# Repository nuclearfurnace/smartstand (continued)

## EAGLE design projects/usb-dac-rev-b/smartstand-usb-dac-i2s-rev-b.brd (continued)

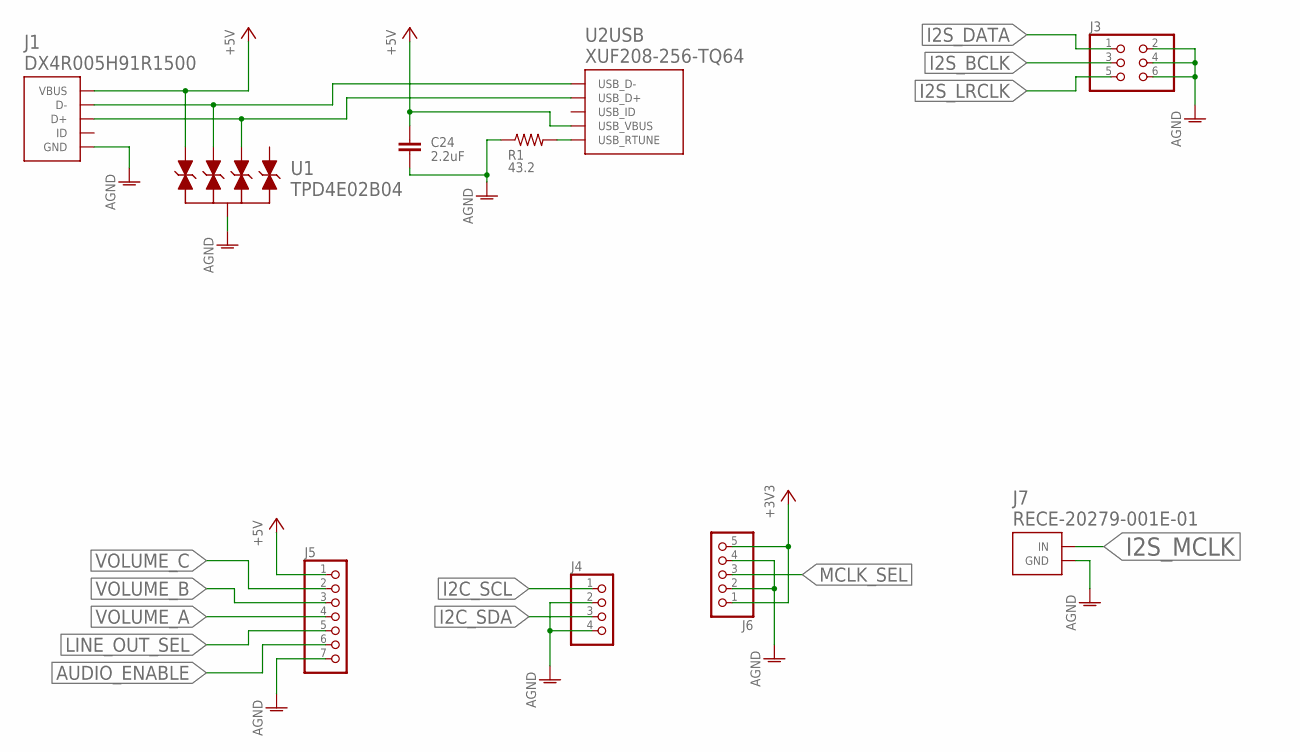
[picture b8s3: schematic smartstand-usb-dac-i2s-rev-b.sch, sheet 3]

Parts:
C24: 2.2uF; C0603
J1: DX4R005H91R1500
J3: PINHD-2X3; 2X03
J4: PINHD-1X4; 1X04
J5: PINHD-1X7; 1X07
J6: PINHD-1X5; 1X05
J7: RECE-20279-001E-01; IPEX-MHF
R1: 43.2; R0402
U1: TPD4E02B04; R-PUSON-N10
U2: XUF208-256-TQ64; TQFP-64-EXPOSED-PAD

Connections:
+3V3: J6.1, J6.5; also elsewhere on the board
+5V: C24.1, J1.P$1 (VBUS), J5.1, U1.P$1 (IO1), U1.P$10 (IO1), U2.P$23 (USB_VBUS); also elsewhere on the board
AGND: C24.2, J1.P$5 (GND), J3.2, J3.4, J3.6, J4.2, J4.4, J5.7, J6.2, J6.4, J7.P$1 (GND), J7.P$2 (GND), R1.1, U1.P$3 (GND), U1.P$8 (GND); also elsewhere on the board
AUDIO_ENABLE: J5.6; also elsewhere on the board
I2C_SCL: J4.1; also elsewhere on the board
I2C_SDA: J4.3; also elsewhere on the board
I2S_BCLK: J3.3; also elsewhere on the board
I2S_DATA: J3.1; also elsewhere on the board
I2S_LRCLK: J3.5; also elsewhere on the board
I2S_MCLK: J7.P$3 (IN); also elsewhere on the board
LINE_OUT_SEL: J5.5; also elsewhere on the board
MCLK_SEL: J6.3; also elsewhere on the board
unnamed: R1.2, U2.P$24 (USB_RTUNE)
USB_D_N: J1.P$2 (D-), U1.P$2 (IO2), U1.P$9 (IO2), U2.P$26 (USB_D-)
USB_D_P: J1.P$3 (D+), U1.P$4 (IO3), U1.P$7 (IO3), U2.P$25 (USB_D+)
VOLUME_A: J5.4; also elsewhere on the board
VOLUME_B: J5.3; also elsewhere on the board
VOLUME_C: J5.2; also elsewhere on the board

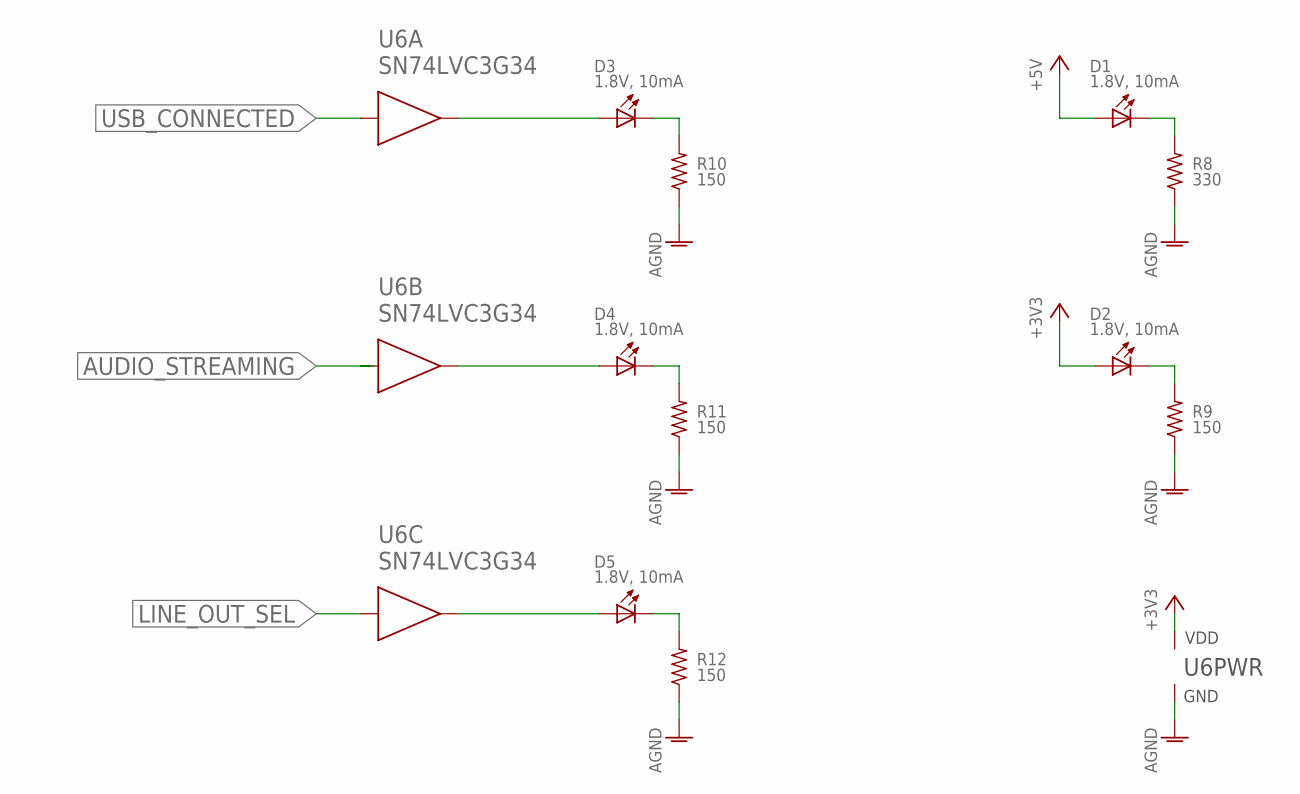
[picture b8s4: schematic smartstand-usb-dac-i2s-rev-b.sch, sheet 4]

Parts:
D1, D2, D3, D4, D5: 1.8V, 10mA; DIALIGHT-0603
R8: 330; R0402
R9, R10, R11, R12: 150; R0402
U6: SN74LVC3G34; R-PDSO-G8

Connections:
+3V3: D2.1 (A), U6.8 (VDD); also elsewhere on the board
+5V: D1.1 (A); also elsewhere on the board
AGND: R8.1, R9.1, R10.1, R11.1, R12.1, U6.4 (GND); also elsewhere on the board
AUDIO_STREAMING: U6.3 (A); also elsewhere on the board
LINE_OUT_SEL: U6.6 (A); also elsewhere on the board
unnamed: D4.1 (A), U6.5 (Y)
unnamed: D1.2 (C), R8.2
unnamed: D2.2 (C), R9.2
unnamed: D3.1 (A), U6.7 (Y)
unnamed: D3.2 (C), R10.2
unnamed: D4.2 (C), R11.2
unnamed: D5.1 (A), U6.2 (Y)
unnamed: D5.2 (C), R12.2
USB_CONNECTED: U6.1 (A); also elsewhere on the board

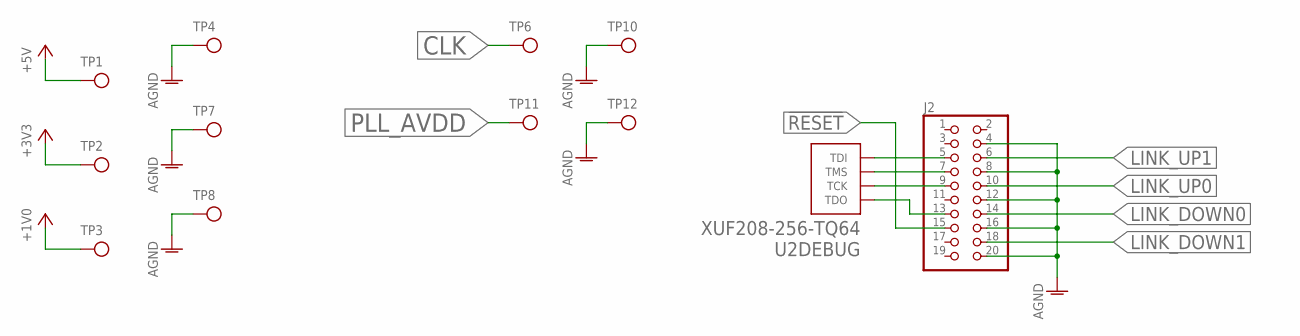
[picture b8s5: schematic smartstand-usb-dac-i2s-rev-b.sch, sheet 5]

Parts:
J2: PINHD-2X10; 2X10
TP1, TP2, TP3, TP6, TP11: TESTPOINT-1.5MM; TESTPOINT-1.5
TP4, TP7, TP8, TP10, TP12: TESTPOINT-1.5MM-SQUARE; TESTPOINT-1.5-SQUARE
U2: XUF208-256-TQ64; TQFP-64-EXPOSED-PAD

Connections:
!RESET: J2.15; also elsewhere on the board
+1V0: TP3.P$1; also elsewhere on the board
+3V3: TP2.P$1; also elsewhere on the board
+5V: TP1.P$1; also elsewhere on the board
AGND: J2.4, J2.8, J2.12, J2.16, J2.20, TP4.P$1, TP7.P$1, TP8.P$1, TP10.P$1, TP12.P$1; also elsewhere on the board
CLK: TP6.P$1; also elsewhere on the board
LINK_DOWN0: J2.14; also elsewhere on the board
LINK_DOWN1: J2.18; also elsewhere on the board
LINK_UP0: J2.10; also elsewhere on the board
LINK_UP1: J2.6; also elsewhere on the board
unnamed: J2.7, U2.P$60 (TMS)
unnamed: J2.9, U2.P$61 (TCK)
unnamed: J2.5, U2.P$62 (TDI)
unnamed: J2.13, U2.P$63 (TDO)
PLL_AVDD: TP11.P$1; also elsewhere on the board

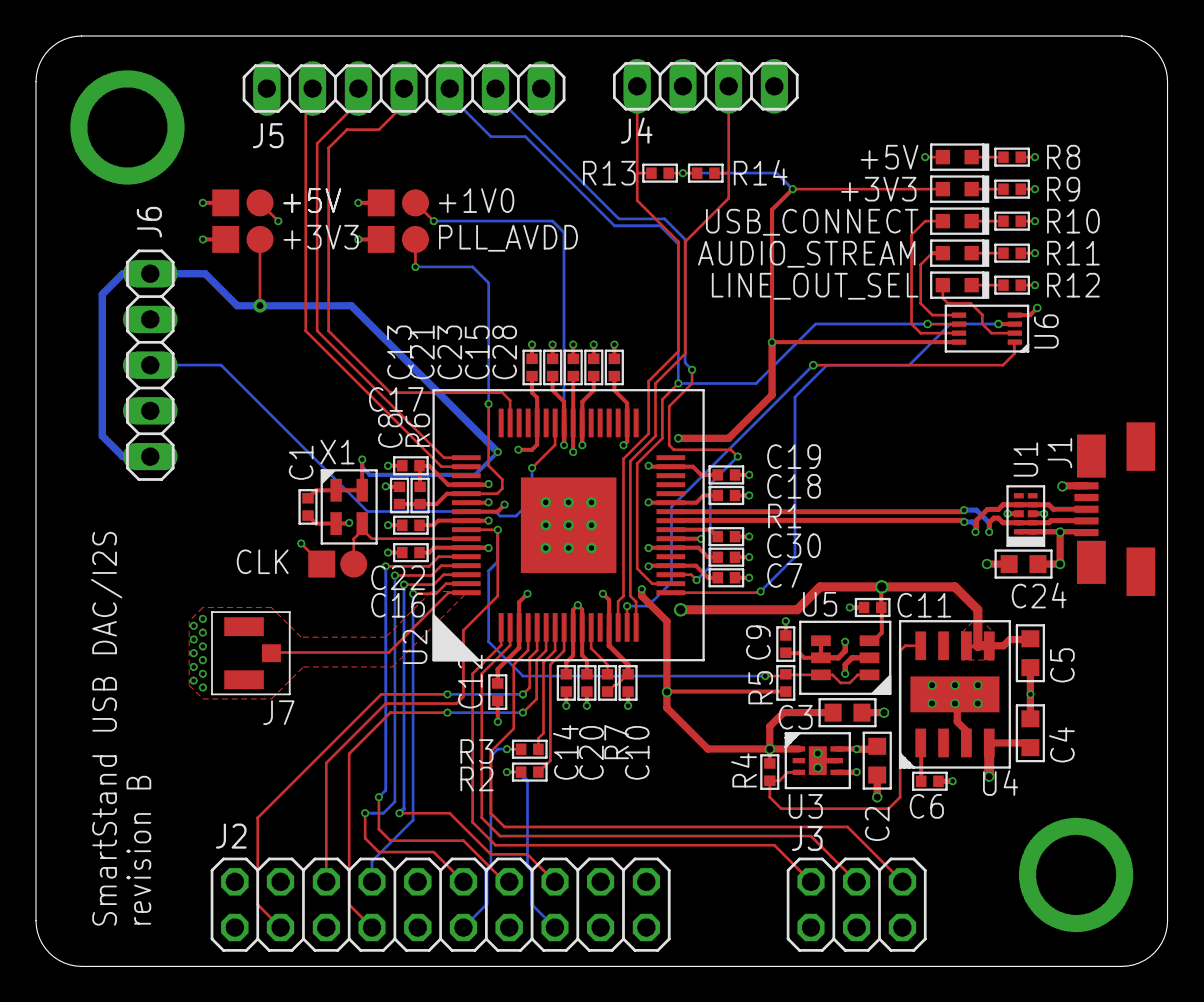
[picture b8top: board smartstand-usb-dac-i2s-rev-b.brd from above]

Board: 4 copper layers, 62.9 x 51.7 mm, 69 parts (0 on the bottom side), 45 nets.

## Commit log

2016-12-16 Initial import.
    This includes all design files as they currently stand, so we won't have
    much history at all, only just tweaks to the final design.
    We have DRC rules and datasheets for many of the major components.
2016-12-17 Ensure all resistors and capacitors in audio path are spec'd correctly.
    Basically just went through and made sure we had 0.1% tolerance on the
    resistors, with the exception of 1% on the outout resistors because
    percision ones (aka current sense resistors ) are $xx.xx, and made sure
    that our capacitors are C0G/NP0. I switched to film capacitors for the
    DC blocking input capacitors on the output stage because values that
    large for C0G/NP0 ceramics don't exist on Mouser.
2016-12-17 Added the datasheet for our USB type B connector.
2016-12-17 Adding part numbers for major components.
2016-12-18 Ignore OS X things like .DS_Store
2016-12-18 Adding more part numbers and fixing incorrect ones.
2016-12-18 Add 3D IDF data for board.
2016-12-20 Fix PJ-002A footprint and remove cream from testpoints.
2016-12-21 Some housekeeping tasks to keep up the schematic.
    Switched from R_US/R_US-VERTICAL to RESISTOR and RESISTOR-HORIZONTAL,
    which brings up in line with our usage of CAPACITOR and
    CAPACITOR-HORIZONTAL. Ultimately, our likelihood of using through-hole
    passives is very, very low, so I'm trying to commit to pruning down our
    rcl (to eventually be named 'passives') library to the most basic/common
    SMD passives footprints and nothing more
2016-12-23 Start of trying to get Travis CI to run our schematic sanity checks.
2016-12-23 Tweaks to the TravisCI config.
2016-12-23 Woops, misspelling.
2016-12-23 testing the tests :P
2016-12-23 Alright, tests catch failures properly so going back to clean.
2016-12-23 Update IDF files.
    This now accounts for the larger hole needed for the positive pin of the
    DC power jack.
2016-12-23 Fixed up the NRJ6HH footprint which let us push it further out.
2016-12-23 Update IDF files.
2016-12-23 Move DRC rules to ecad-tooling.
2016-12-23 Switch over to renamed libraries.
2016-12-24 Converting over to our simplified passives.
2016-12-24 More library tweaks.
2016-12-24 Fix some part number issues.
2016-12-26 Minor board layout tweaks.
    Adjusted how we route the USB signals to better take advantage of the
    type B connector, which now lets us avoid a layer transition. We're
    about 37mils difference between the pair lengths which is well within
    bounds of the 100ps skew allowed by the USB specification.
    Also, I mistakenly forgot to route power into the pigtail between the
    main board and the headphone detection daughterboard, which is now
2016-12-26 Adjust the I2C pinout on the daughterboard connector.
    This will let us have cleaner routing on the small daughterboard which
    houses the proximity sensor.
2016-12-26 Add the rev A of the headphone detection daughterboard.
    This board houses the VCNL4010 proximity sensor which will be embedded
    in the stand arm to detect when the headphones are present/sitting on
    the arm.
    We'll speak to it via I2C in a simple polling fashion to determine the
    state of docking.
2016-12-27 Big updates to the headphone detection daughterboard.
    In no particular order:
    - we're now using the VL6180X (micro LIDAR, basically)
    - which needs 2V8 so we have an on-board regulator
    - which means we need to interface with 3V3 I2C logic so we
    - added level translation FETs for each I2C line
    - added test points for the two supply rails
2016-12-27 Rename schematic/board files to match existing naming scheme.
2016-12-27 Run design checks on the headphone detection daughterboard.
2016-12-27 Adding part numbers to schematic.
2016-12-27 Updated component choice to better alternative.
2016-12-27 Add BOM exclusions to frames/testpoints.
2016-12-27 Add fiducials and fix ERC/DRC errors.
2016-12-28 Add BOM exclude to fiducials.
2017-01-03 Switch everything to vector fonts and add LEDs for knob illumination.
    We added LEDs around the volume control potentiometer so that we could
    get an underlighting effect on the volume knob. The base now has
    corresponding holes inside the support structure/cavity that the volume
    knob sits around, and since we engineered it so that the knob has a
    small gap from the base, the new holes added will allow light to escape
    all the way out, and under the volume knob, providing a soft white glow
2017-01-06 Add volume knob illumination LEDs.
2017-01-06 Create LED evaluation board for volume knob lighting.
    We're just making a simple board here that emulates the layout of the
    LEDs on the main board, so we can see how hot things get and how much
    actual light there is, since we want enough to "escape" as it goes
    through webbed-out passages inside the volume knob.
2017-01-06 DFM tweaks to the headphone detection daughterboard.
    Switched to vector fonts to better repicate what will end up on our
    actual boards, and tweaked net label sizes.
    Also switched one capacitor to a different package/PN for cost reasons.
2017-01-19 Created a rev B of the headphone detection board.
    Some simple changes:
    - added a third fiducial to allow better alignment
    - adjusted placement/routing of regulator to account for fiducial
    - updated footprint of VL6180X to include pin 1 indicator
    - updated board info to indicate rev B
2017-01-19 Update TravisCI configuration to account for new revision.
2017-02-02 Add Nuclear Furnace logo to headphone detection board.
2017-02-02 Simple tweaks to the schematic for readability.
2017-02-09 Pull enclosure files into the repository.
    Initially, I had the enclosure files in a separate repository. As I get
    closer to "cutting" a final revision of the board, though, it makes more
    sense to bundle it all in one so that I can tag the commit that
    represents the finalized board *and* enclosure, ensuring proper fit,
    etc.
2017-02-23 Shift headphone jack outwards to before more flush.
2017-02-23 Clean up some wiring; better clearances and 'tightness'
2017-02-23 Add mounting hole between USB jack and DC power jack.
    That area was a little flimsy and didn't have a mounting hole parallel
    to the edge, leaving too much of an overhang for my tastes.
    Luckily, we had just enough space between the connectors to fit in a
    mounting hole, and so, voila!
2017-02-23 Adjust power jack footprint and placement.
    After getting the test boards back, the PTH fitment is super loose, and
    because of that, it's hard to tell if things are positioned correctly.
    I went and back took real measurements of the pins, cross-referenced
    with what the datasheet says, and ran the numbers again using the IPC
    specification for the tightest fit.
    I also adjusted the footprint to better account for the centerline of
2017-02-23 Adjust RCA jack placement.
    After measuring with the test boards, we had about 1mm worth of distance
    from the front face of the RCA jacks to the edge of the board.
    Now the jack is shifted over to sit flush with the board edge, exposing
    that extra 1mm outside of the enclosure. This gets us to a more
    comfortable 6mm of exposed jack, for better plug seating.
2017-02-23 Updating to a less chunky footprint doc layer.
2017-02-23 Add IDF files for board.
2017-02-23 Remove MCAD filles from the top-level of the project folder.
2017-02-24 Incorporate the latest IDF changes into the model.
    This involves the nudging of connectors/ports on the board to maximize
    the engagement we can achieve.
    I also reworked some of the mates, and, I think, generally cleaned
    things up everrrrrr so slightly.
    I also regenerated the STL files after making said changes.
2017-02-24 Clean up some routing of the relay control lines.
2017-02-24 Tightening up fiducial to processor.
2017-09-12 Start working on rev B on the USB DAC/Amplifier board.
    I think I got far enough originally, even without building, to consider
    the design doable with the hardware and size constraints.
    Rev B will feature, primarily, a reduced average footprint: we'll split
    the actual audio processing and the volume control, which will let us
    avoid an oddly-shaped board. The board shape was inflating the pricing
    on board manufacture due to the overall high bounding box dimensions.
2017-09-13 Start shuffling things off into the main section.
2017-09-13 First rough pass at the slimdown.
    I've roughly adjusted the dimensions and shoved everything in there.
    The routing isn't half bad, but it's gonna need a lot of tweaks, namely
    to get things in a better position, with better trace/space, with
    cleaner silkscreen layout.
    There's still some angles and airwires and obvious stuff to sort out
    but, otherwise, a good first pass.
2017-09-14 More fixups and cleaup.
    Not too much changed here, but the airwires have been cleaned up.
    Still need to make sure that the connector offset from the edge is good,
    as well as go through each subsystem and redo functional/design checks.
    After that, I think I can properly clean up and tidy up the routing.
2018-01-14 Torch the old enclosure design.
    Decided I really want something made out of wood, so we need to ditch
    the super curvy and abstract design some something simpler and more
    straight forward.
2018-03-22 Start attributizing things to help develop tooling.
2018-03-31 Lots of updates and tweaks.
    This is the locked version for rev A of the volume control board.
2018-09-07 Lots of cleanup.
    Fixing up some incorrect MPNs and package sizes for bulk capacitance, and cleaning up DRC bits. Also trying to move some bulk capacitance around the board to create a better supply plane.
2018-09-09 More DFM tune ups.
    Just trying to simplify the BOM and make the sourcing easier.
2018-09-24 Continuing to optimize the design for DFM.
2018-09-26 start switching over to simplified bypassing
2018-09-26 More BOM tweaking.
    We had some caps that were not sized properly for their expected voltages, so we've fixed that up, and we've added MPNs where necessary.
2018-10-28 Cleaning up some of the power circuitry.
    A lot of generic cleanup here:
    - capacitor availability is painful, so reworking that
    - no need to use the smallest via possible when fewer bigger ones will do
    - use ranks to better allow flood pours to coexist
